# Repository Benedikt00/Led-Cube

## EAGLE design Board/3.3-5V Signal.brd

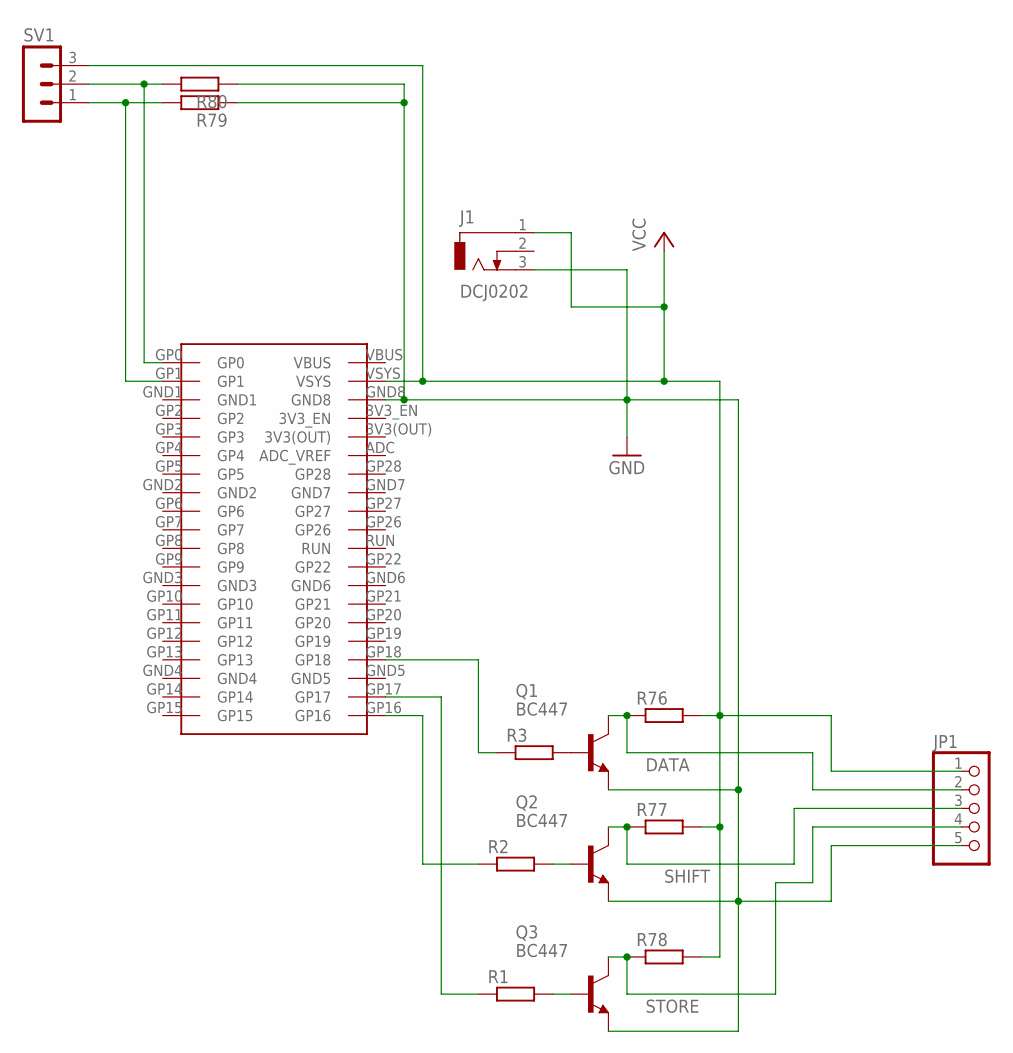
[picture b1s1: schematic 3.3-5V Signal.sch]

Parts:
J1: DCJ0202
JP1: PINHD-1X5; 1X05
Q1, Q2, Q3: BC447; TO92-EBC
R1, R2, R3, R76, R77, R78, R79, R80: R-EU_0207/10; 0207/10
SV1: MA03-1
U$2: PI_PICO

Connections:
DATA: JP1.2, Q1.C, R76.1
GND: J1.3, JP1.5, Q1.E, Q2.E, Q3.E, R79.1, R80.1, U$2.GND8
unnamed: R1.1, U$2.GP17
unnamed: Q3.B, R1.2
unnamed: Q2.B, R2.2
unnamed: Q1.B, R3.2
unnamed: R3.1, U$2.GP18
unnamed: R2.1, U$2.GP16
unnamed: R80.2, SV1.2, U$2.GP0
unnamed: R79.2, SV1.1, U$2.GP1
SHIFT: JP1.3, Q2.C, R77.1
STORE: JP1.4, Q3.C, R78.1
VCC: J1.1, JP1.1, R76.2, R77.2, R78.2, SV1.3, U$2.VSYS

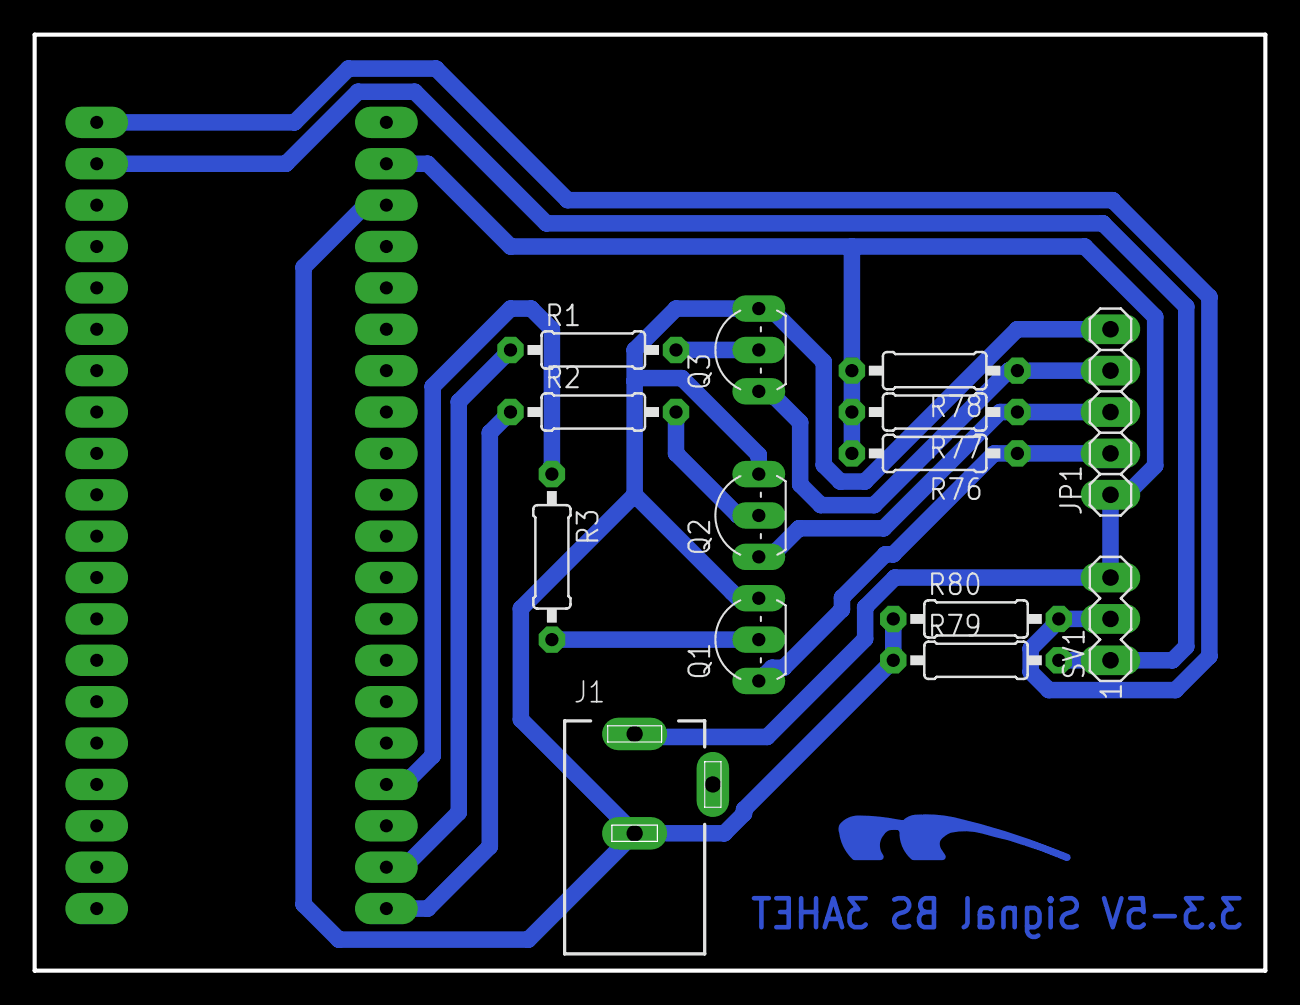
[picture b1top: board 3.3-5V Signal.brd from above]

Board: 2 copper layers, 75.5 x 57.5 mm, 16 parts (0 on the bottom side), 13 nets.

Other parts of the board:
U$3: LOGOBOT_15

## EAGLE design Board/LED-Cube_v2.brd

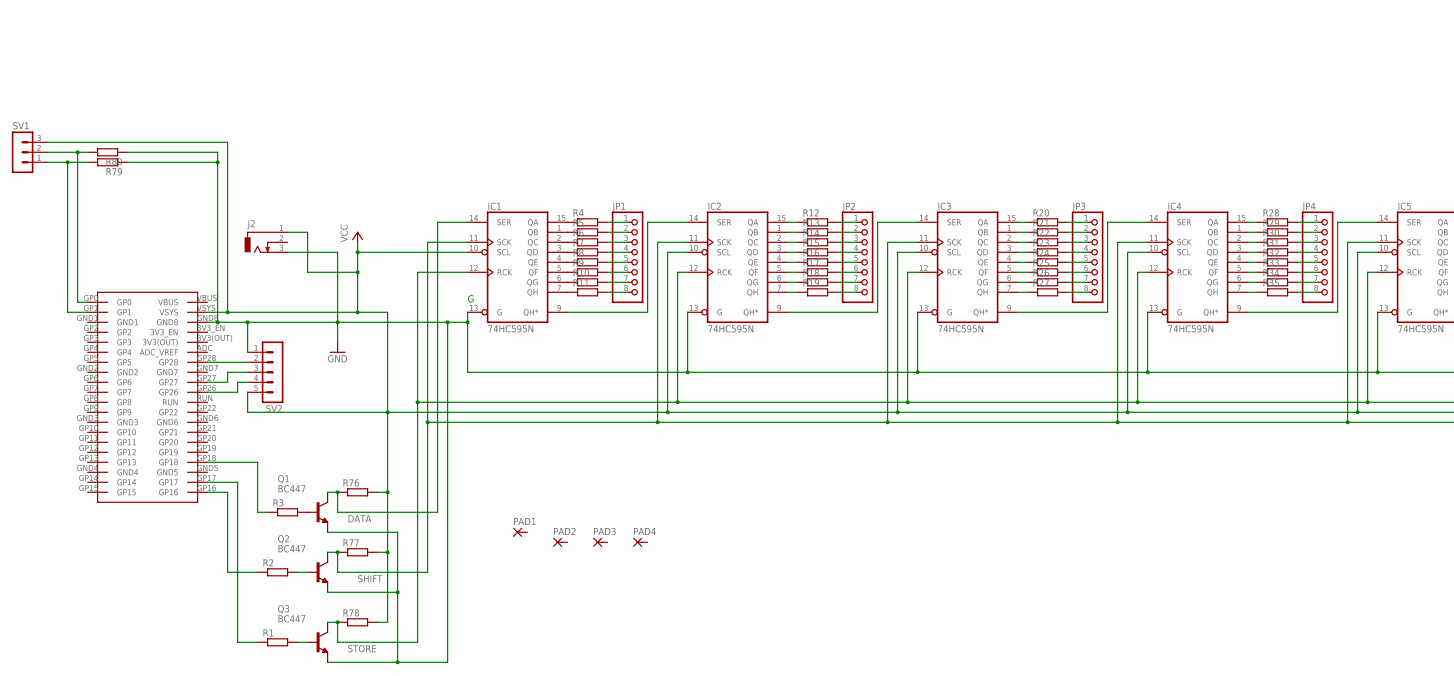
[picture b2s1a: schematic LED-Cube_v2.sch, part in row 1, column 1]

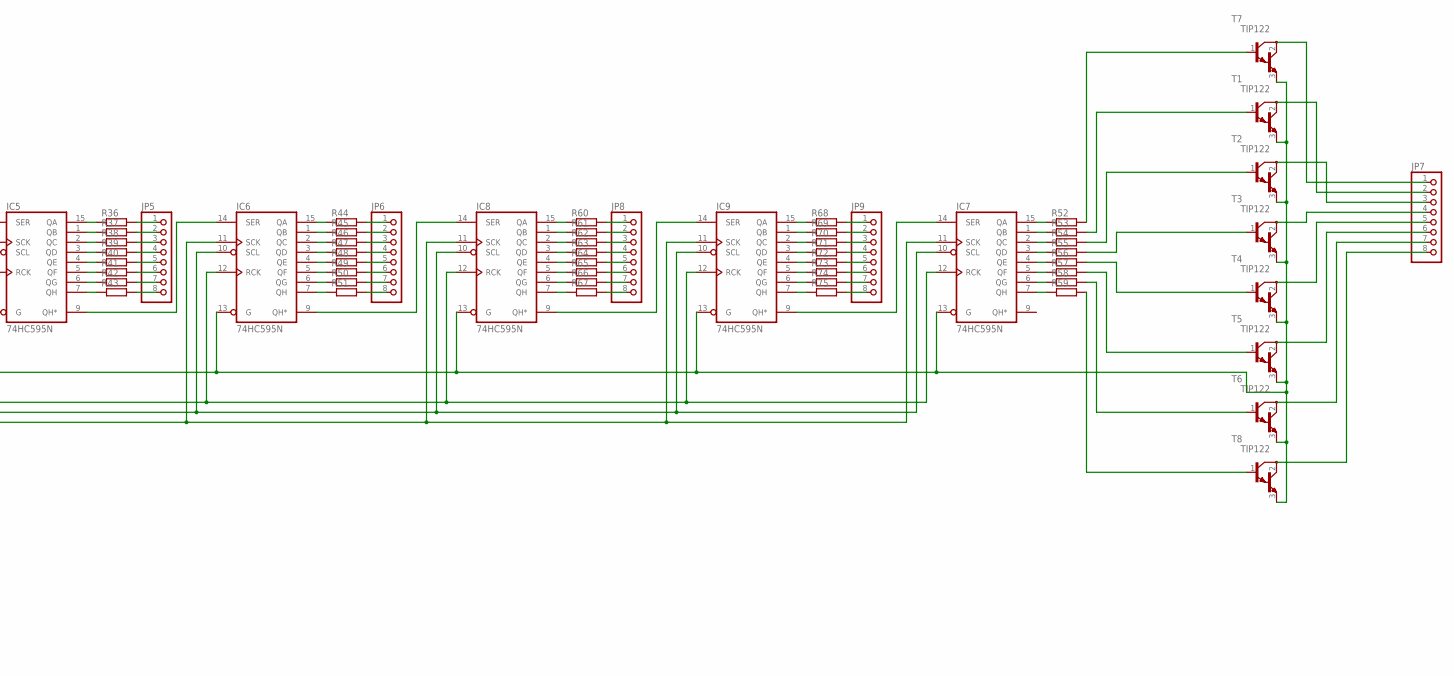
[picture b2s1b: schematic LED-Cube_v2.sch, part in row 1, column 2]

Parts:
IC1, IC2, IC3, IC4, IC5, IC6, IC7, IC8, IC9: 74HC595N; DIL16
J2: DCJ0303
JP1, JP2, JP3, JP4, JP5, JP6, JP7, JP8, JP9: PINHD-1X8; 1X08
PAD1, PAD2, PAD3, PAD4: 3,81/1,4
Q1, Q2, Q3: BC447; TO92-EBC
R1, R2, R3, R4, R5, R6, R7, R8, R9, R10, R11, R12, R13, R14, R15, R16, R17, R18, R19, R20, R21, R22, R23, R24, R25, R26, R27, R28, R29, R30, R31, R32, R33, R34, R35, R36, R37, R38, R39, R40, R41, R42, R43, R44, R45, R46, R47, R48, R49, R50, R51, R52, R53, R54, R55, R56, R57, R58, R59, R60, R61, R62, R63, R64, R65, R66, R67, R68, R69, R70, R71, R72, R73, R74, R75, R76, R77, R78, R79, R80: R-EU_0207/10; 0207/10
SV1: MA03-1
SV2: MA05-1
T1, T2, T3, T4, T5, T6, T7, T8: TIP122; TO220
U$2: PI_PICO

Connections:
DATA: IC1.14 (SER), Q1.C, R76.1
GND: IC1.8 (GND), IC1.13 (G), IC2.8 (GND), IC2.13 (G), IC3.8 (GND), IC3.13 (G), IC4.8 (GND), IC4.13 (G), IC5.8 (GND), IC5.13 (G), IC6.8 (GND), IC6.13 (G), IC7.8 (GND), IC7.13 (G), IC8.8 (GND), IC8.13 (G), IC9.8 (GND), IC9.13 (G), J2.3, Q1.E, Q2.E, Q3.E, R79.1, R80.1, SV2.1, T1.3 (E), T2.3 (E), T3.3 (E), T4.3 (E), T5.3 (E), T6.3 (E), T7.3 (E), T8.3 (E), U$2.GND8
unnamed: R1.1, U$2.GP17
unnamed: Q3.B, R1.2
unnamed: SV2.4, U$2.GP26
unnamed: Q2.B, R2.2
unnamed: Q1.B, R3.2
unnamed: R3.1, U$2.GP18
unnamed: R2.1, U$2.GP16
unnamed: IC1.15 (QA), R4.1
unnamed: IC1.5 (QF), R9.1
unnamed: IC1.6 (QG), R10.1
unnamed: IC1.7 (QH), R11.1
unnamed: JP1.1, R4.2
unnamed: JP1.2, R5.2
unnamed: IC1.1 (QB), R5.1
unnamed: IC1.2 (QC), R6.1
unnamed: IC1.3 (QD), R7.1
unnamed: IC1.4 (QE), R8.1
unnamed: JP1.3, R6.2
unnamed: JP1.4, R7.2
unnamed: JP1.5, R8.2
unnamed: JP1.6, R9.2
unnamed: JP1.7, R10.2
unnamed: JP1.8, R11.2
unnamed: IC2.1 (QB), R13.1
unnamed: IC2.2 (QC), R14.1
unnamed: IC2.3 (QD), R15.1
unnamed: IC2.4 (QE), R16.1
unnamed: IC1.9 (QH*), IC2.14 (SER)
unnamed: IC2.15 (QA), R12.1
unnamed: IC2.5 (QF), R17.1
unnamed: IC2.6 (QG), R18.1
unnamed: IC2.7 (QH), R19.1
unnamed: JP2.1, R12.2
unnamed: JP2.2, R13.2
unnamed: JP2.3, R14.2
unnamed: JP2.4, R15.2
unnamed: JP2.5, R16.2
unnamed: JP2.6, R17.2
unnamed: JP2.7, R18.2
unnamed: JP2.8, R19.2
unnamed: R80.2, SV1.2, U$2.GP0
unnamed: IC2.9 (QH*), IC3.14 (SER)
unnamed: R79.2, SV1.1, U$2.GP1
unnamed: IC3.1 (QB), R21.1
unnamed: IC3.2 (QC), R22.1
unnamed: IC3.3 (QD), R23.1
unnamed: IC3.4 (QE), R24.1
unnamed: IC3.15 (QA), R20.1
unnamed: IC3.5 (QF), R25.1
unnamed: IC3.6 (QG), R26.1
unnamed: IC3.7 (QH), R27.1
unnamed: JP3.1, R20.2
unnamed: JP3.2, R21.2
unnamed: JP3.3, R22.2
unnamed: JP3.4, R23.2
unnamed: JP3.5, R24.2
unnamed: JP3.6, R25.2
unnamed: JP3.7, R26.2
unnamed: JP3.8, R27.2
unnamed: IC7.15 (QA), R52.1
unnamed: IC3.9 (QH*), IC4.14 (SER)
unnamed: IC7.1 (QB), R53.1
unnamed: IC4.1 (QB), R29.1
unnamed: IC4.2 (QC), R30.1
unnamed: IC4.3 (QD), R31.1
unnamed: IC4.4 (QE), R32.1
unnamed: IC4.15 (QA), R28.1
unnamed: IC4.5 (QF), R33.1
unnamed: IC4.6 (QG), R34.1
unnamed: IC4.7 (QH), R35.1
unnamed: JP4.1, R28.2
unnamed: JP4.2, R29.2
unnamed: JP4.3, R30.2
unnamed: JP4.4, R31.2
unnamed: JP4.5, R32.2
unnamed: JP4.6, R33.2
unnamed: JP4.7, R34.2
unnamed: JP4.8, R35.2
unnamed: IC7.2 (QC), R54.1
unnamed: IC4.9 (QH*), IC5.14 (SER)
unnamed: IC7.3 (QD), R55.1
unnamed: IC5.1 (QB), R37.1
unnamed: IC5.2 (QC), R38.1
unnamed: IC5.3 (QD), R39.1
unnamed: IC5.4 (QE), R40.1
unnamed: IC5.15 (QA), R36.1
unnamed: IC5.5 (QF), R41.1
unnamed: IC5.6 (QG), R42.1
unnamed: IC5.7 (QH), R43.1
unnamed: JP5.1, R36.2
unnamed: JP5.2, R37.2
unnamed: JP5.3, R38.2
unnamed: JP5.4, R39.2
unnamed: JP5.5, R40.2
unnamed: JP5.6, R41.2
unnamed: JP5.7, R42.2
unnamed: JP5.8, R43.2
unnamed: IC7.4 (QE), R56.1
unnamed: IC5.9 (QH*), IC6.14 (SER)
unnamed: IC7.5 (QF), R57.1
unnamed: IC6.1 (QB), R45.1
unnamed: IC6.2 (QC), R46.1
unnamed: IC6.3 (QD), R47.1
unnamed: IC6.4 (QE), R48.1
unnamed: IC6.15 (QA), R44.1
unnamed: IC6.5 (QF), R49.1
unnamed: IC6.6 (QG), R50.1
unnamed: IC6.7 (QH), R51.1
unnamed: JP6.1, R44.2
unnamed: JP6.2, R45.2
unnamed: JP6.3, R46.2
unnamed: JP6.4, R47.2
unnamed: JP6.5, R48.2
unnamed: JP6.6, R49.2
unnamed: JP6.7, R50.2
unnamed: JP6.8, R51.2
unnamed: IC7.6 (QG), R58.1
unnamed: SV2.3, U$2.GP27
unnamed: IC7.7 (QH), R59.1
unnamed: R52.2, T7.1 (B)
unnamed: R53.2, T1.1 (B)
unnamed: R54.2, T2.1 (B)
unnamed: R55.2, T3.1 (B)
unnamed: R56.2, T4.1 (B)
unnamed: R57.2, T5.1 (B)
unnamed: R58.2, T6.1 (B)
unnamed: R59.2, T8.1 (B)
unnamed: JP7.1, T7.2 (C)
unnamed: JP7.2, T1.2 (C)
unnamed: JP7.3, T2.2 (C)
unnamed: JP7.4, T3.2 (C)
unnamed: JP7.5, T4.2 (C)
unnamed: JP7.6, T5.2 (C)
unnamed: JP7.7, T6.2 (C)
unnamed: JP7.8, T8.2 (C)
unnamed: IC6.9 (QH*), IC8.14 (SER)
unnamed: IC8.1 (QB), R61.1
unnamed: IC8.2 (QC), R62.1
unnamed: IC8.3 (QD), R63.1
unnamed: IC8.4 (QE), R64.1
unnamed: IC8.15 (QA), R60.1
unnamed: IC8.5 (QF), R65.1
unnamed: IC8.6 (QG), R66.1
unnamed: IC8.7 (QH), R67.1
unnamed: JP8.1, R60.2
unnamed: JP8.2, R61.2
unnamed: JP8.3, R62.2
unnamed: JP8.4, R63.2
unnamed: JP8.5, R64.2
unnamed: JP8.6, R65.2
unnamed: JP8.7, R66.2
unnamed: JP8.8, R67.2
unnamed: SV2.2, U$2.GP28
unnamed: IC8.9 (QH*), IC9.14 (SER)
unnamed: IC9.1 (QB), R69.1
unnamed: IC9.2 (QC), R70.1
unnamed: IC9.3 (QD), R71.1
unnamed: IC9.4 (QE), R72.1
unnamed: IC9.15 (QA), R68.1
unnamed: IC9.5 (QF), R73.1
unnamed: IC9.6 (QG), R74.1
unnamed: IC9.7 (QH), R75.1
unnamed: JP9.1, R68.2
unnamed: JP9.2, R69.2
unnamed: JP9.3, R70.2
unnamed: JP9.4, R71.2
unnamed: JP9.5, R72.2
unnamed: JP9.6, R73.2
unnamed: JP9.7, R74.2
unnamed: JP9.8, R75.2
unnamed: IC7.14 (SER), IC9.9 (QH*)
SHIFT: IC1.11 (SCK), IC2.11 (SCK), IC3.11 (SCK), IC4.11 (SCK), IC5.11 (SCK), IC6.11 (SCK), IC7.11 (SCK), IC8.11 (SCK), IC9.11 (SCK), Q2.C, R77.1
STORE: IC1.12 (RCK), IC2.12 (RCK), IC3.12 (RCK), IC4.12 (RCK), IC5.12 (RCK), IC6.12 (RCK), IC7.12 (RCK), IC8.12 (RCK), IC9.12 (RCK), Q3.C, R78.1
VCC: IC1.10 (SCL), IC1.16 (VCC), IC2.10 (SCL), IC2.16 (VCC), IC3.10 (SCL), IC3.16 (VCC), IC4.10 (SCL), IC4.16 (VCC), IC5.10 (SCL), IC5.16 (VCC), IC6.10 (SCL), IC6.16 (VCC), IC7.10 (SCL), IC7.16 (VCC), IC8.10 (SCL), IC8.16 (VCC), IC9.10 (SCL), IC9.16 (VCC), J2.1, R76.2, R77.2, R78.2, SV1.3, SV2.5, U$2.VSYS

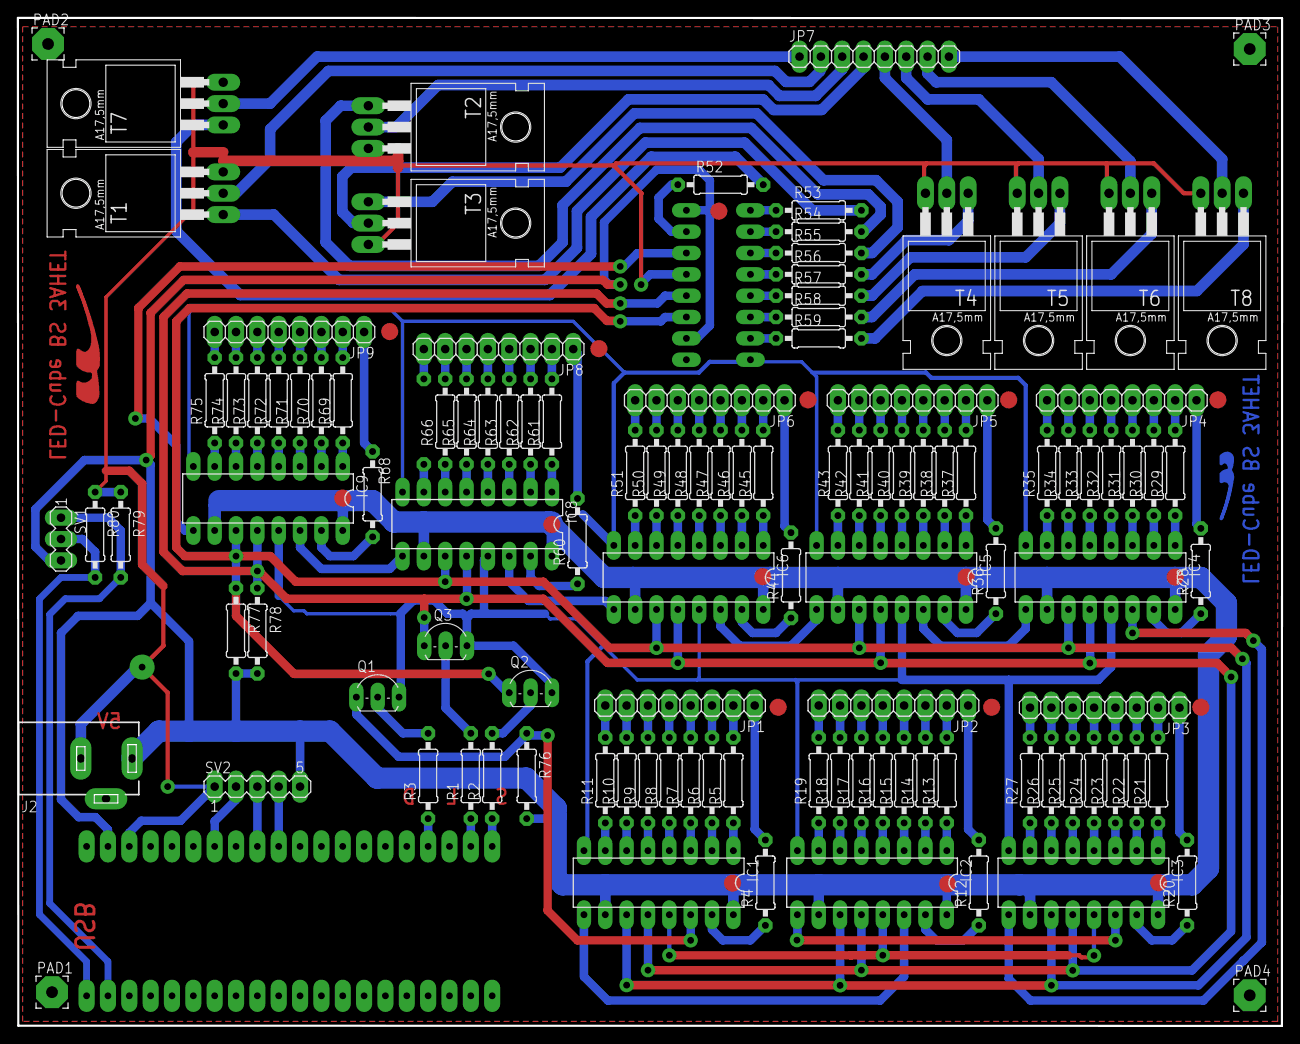
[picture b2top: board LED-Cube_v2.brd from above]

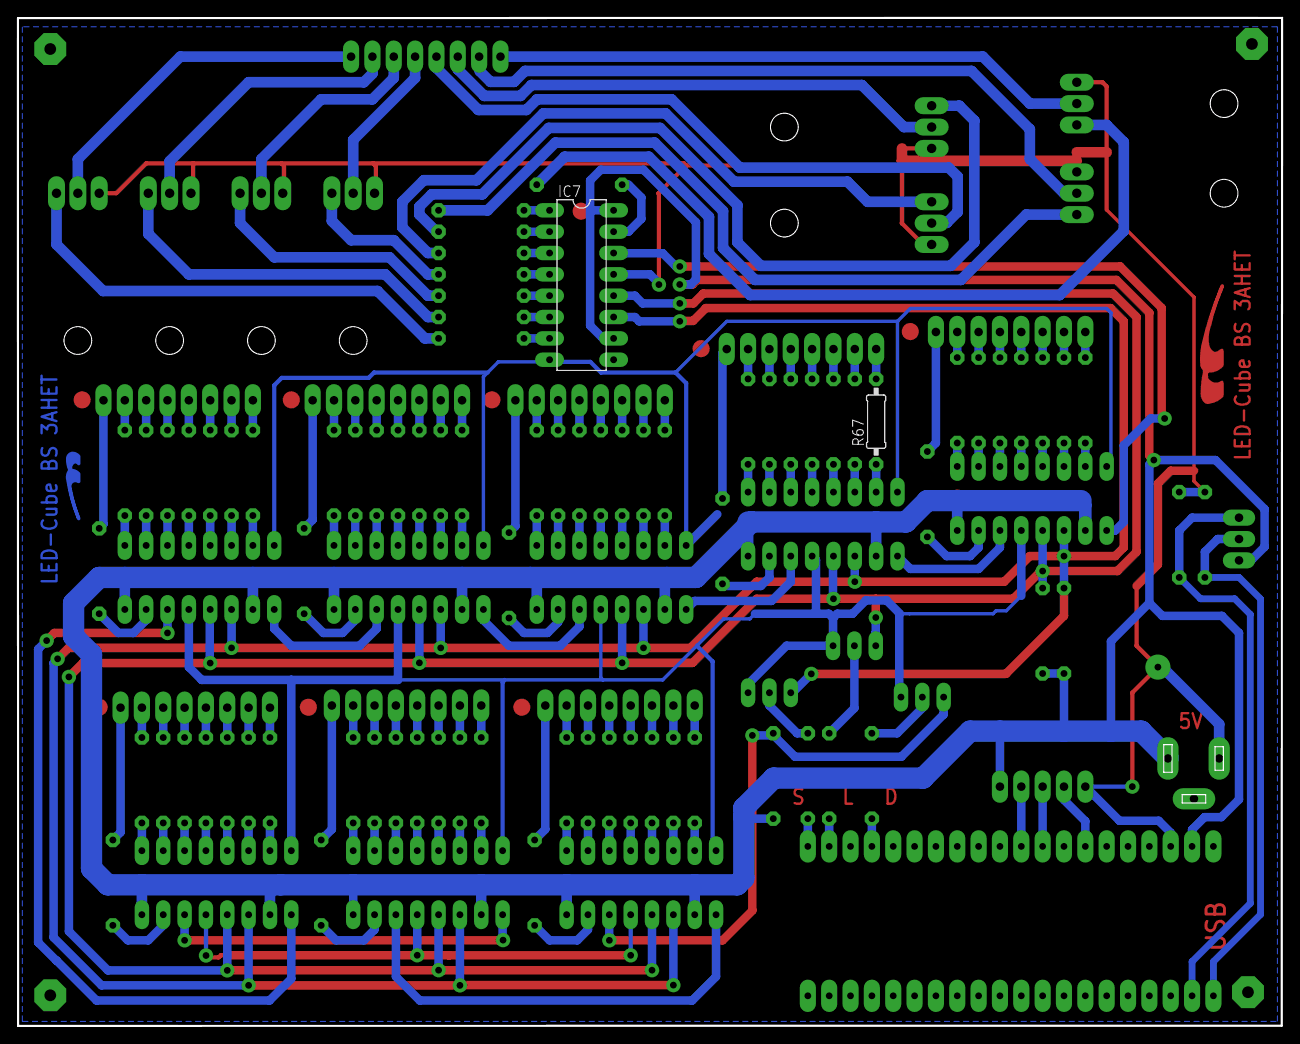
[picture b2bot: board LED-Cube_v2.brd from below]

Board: 2 copper layers, 150.4 x 120.0 mm, 119 parts (2 on the bottom side), 176 nets.

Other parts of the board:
U$1: LOGOBOT_8
U$3: LOGOTOP_15

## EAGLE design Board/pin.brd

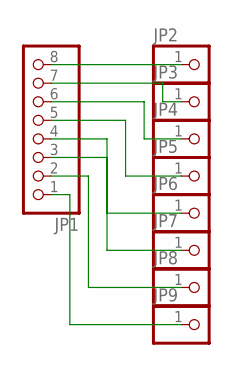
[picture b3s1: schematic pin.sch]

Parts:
JP1: PINHD-1X8; 1X08
JP2, JP3, JP4, JP5, JP6, JP7, JP8, JP9: PINHD-1X1; 1X01

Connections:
unnamed: JP1.8, JP2.1
unnamed: JP1.7, JP3.1
unnamed: JP1.6, JP4.1
unnamed: JP1.5, JP5.1
unnamed: JP1.4, JP6.1
unnamed: JP1.3, JP7.1
unnamed: JP1.2, JP8.1
unnamed: JP1.1, JP9.1

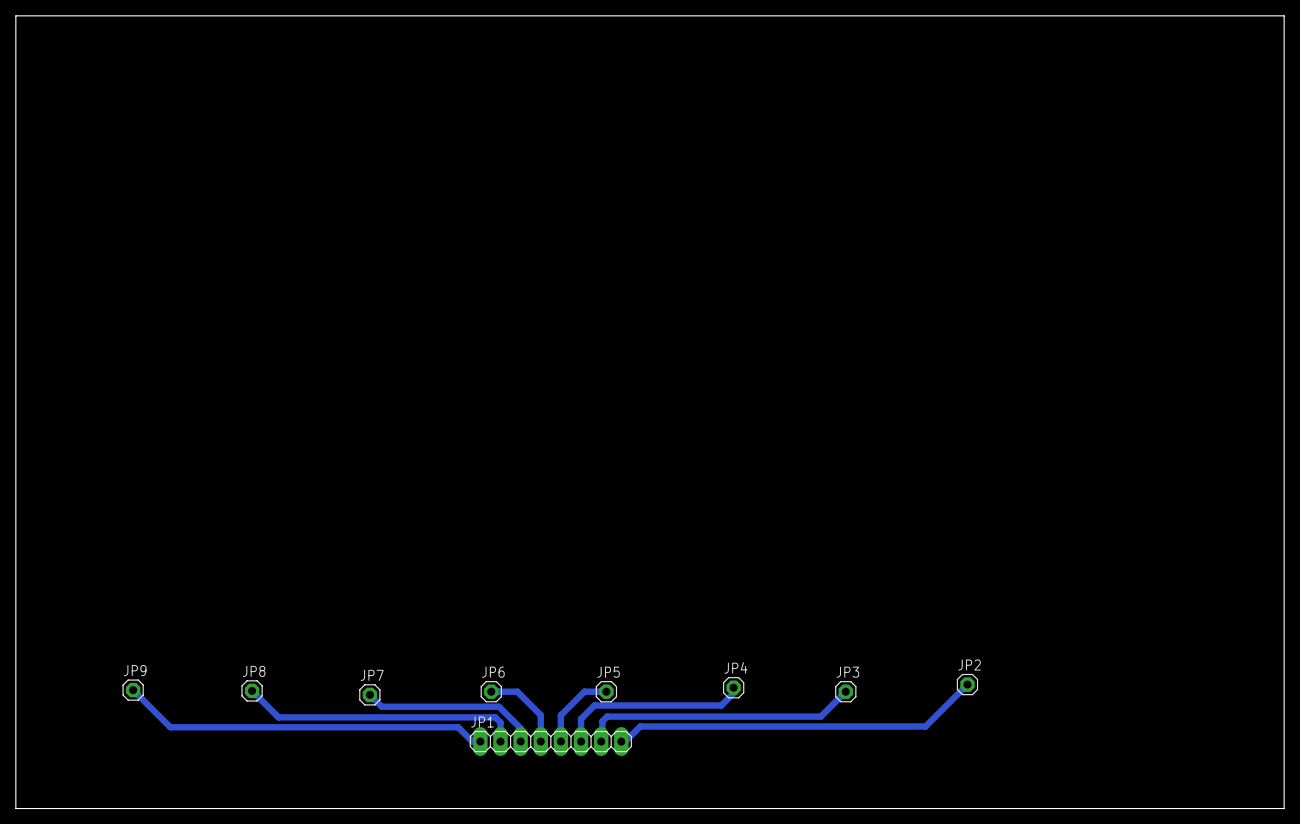
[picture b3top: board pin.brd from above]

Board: 2 copper layers, 160.0 x 100.0 mm, 9 parts (0 on the bottom side), 8 nets.

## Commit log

2022-10-03 031022
2022-11-08 schaltplan
2022-11-14 board
2022-11-30 more
2023-02-21 new board
2024-01-09 last
